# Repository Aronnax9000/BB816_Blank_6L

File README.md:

# BB816_Blank_6L
Blank 6 layer template for BB816 PCB development

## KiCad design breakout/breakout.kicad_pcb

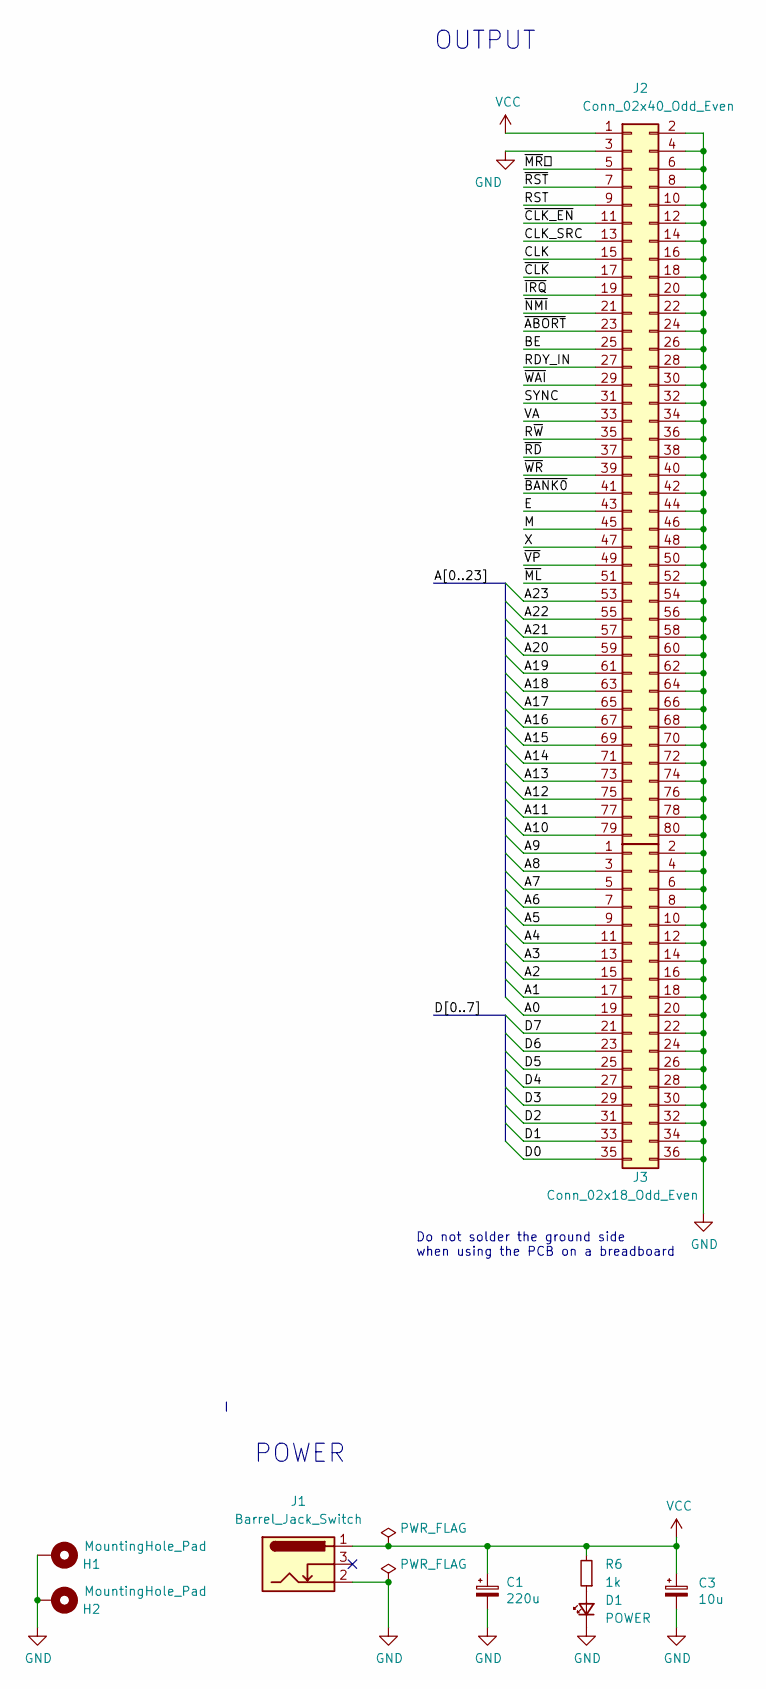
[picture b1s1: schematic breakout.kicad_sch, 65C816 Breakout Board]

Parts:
C1: 220u; CP_Radial_D6.3mm_P2.50mm
C3: 10u; CP_Radial_D4.0mm_P1.50mm
D1: POWER; LED_D3.0mm
H1, H2: MountingHole_Pad; MountingHole_3.2mm_M3_Pad
J1: Barrel_Jack_Switch; BarrelJack_Horizontal
J2: Conn_02x40_Odd_Even; PinHeader_2x40_P2.54mm_Vertical
J3: Conn_02x18_Odd_Even; PinHeader_2x18_P2.54mm_Vertical
R6: 1k; R_Axial_DIN0207_L6.3mm_D2.5mm_P7.62mm_Horizontal

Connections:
/A0: J3.19
/A1: J3.17
/A2: J3.15
/A3: J3.13
/A4: J3.11
/A5: J3.9
/A6: J3.7
/A7: J3.5
/A8: J3.3
/A9: J3.1
/A10: J2.79
/A11: J2.77
/A12: J2.75
/A13: J2.73
/A14: J2.71
/A15: J2.69
/A16: J2.67
/A17: J2.65
/A18: J2.63
/A19: J2.61
/A20: J2.59
/A21: J2.57
/A22: J2.55
/A23: J2.53
/BE: J2.25
/CLK: J2.15
/CLK_SRC: J2.13
/D0: J3.35
/D1: J3.33
/D2: J3.31
/D3: J3.29
/D4: J3.27
/D5: J3.25
/D6: J3.23
/D7: J3.21
/E: J2.43
/M: J2.45
/RDY_IN: J2.27
/RST: J2.9
/R~W: J2.35
/SYNC: J2.31
/VA: J2.33
/X: J2.47
/~ABORT: J2.23
/~BANK0: J2.41
/~CLK_EN: J2.11
/~CLK: J2.17
/~IRQ: J2.19
/~ML: J2.51
/~MR⎒: J2.5
/~NMI: J2.21
/~RD: J2.37
/~RST: J2.7
/~VP: J2.49
/~WAI: J2.29
/~WR: J2.39
GND: C1.2, C3.2, D1.1 (K), H1.1, H2.1, J1.2, J2.2, J2.3, J2.4, J2.6, J2.8, J2.10, J2.12, J2.14, J2.16, J2.18, J2.20, J2.22, J2.24, J2.26, J2.28, J2.30, J2.32, J2.34, J2.36, J2.38, J2.40, J2.42, J2.44, J2.46, J2.48, J2.50, J2.52, J2.54, J2.56, J2.58, J2.60, J2.62, J2.64, J2.66, J2.68, J2.70, J2.72, J2.74, J2.76, J2.78, J2.80, J3.2, J3.4, J3.6, J3.8, J3.10, J3.12, J3.14, J3.16, J3.18, J3.20, J3.22, J3.24, J3.26, J3.28, J3.30, J3.32, J3.34, J3.36
unnamed: D1.2 (A), R6.1
VCC: C1.1, C3.1, J1.1, J2.1, R6.2

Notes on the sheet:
Do not solder the ground side when using the PCB on a breadboard
POWER
OUTPUT

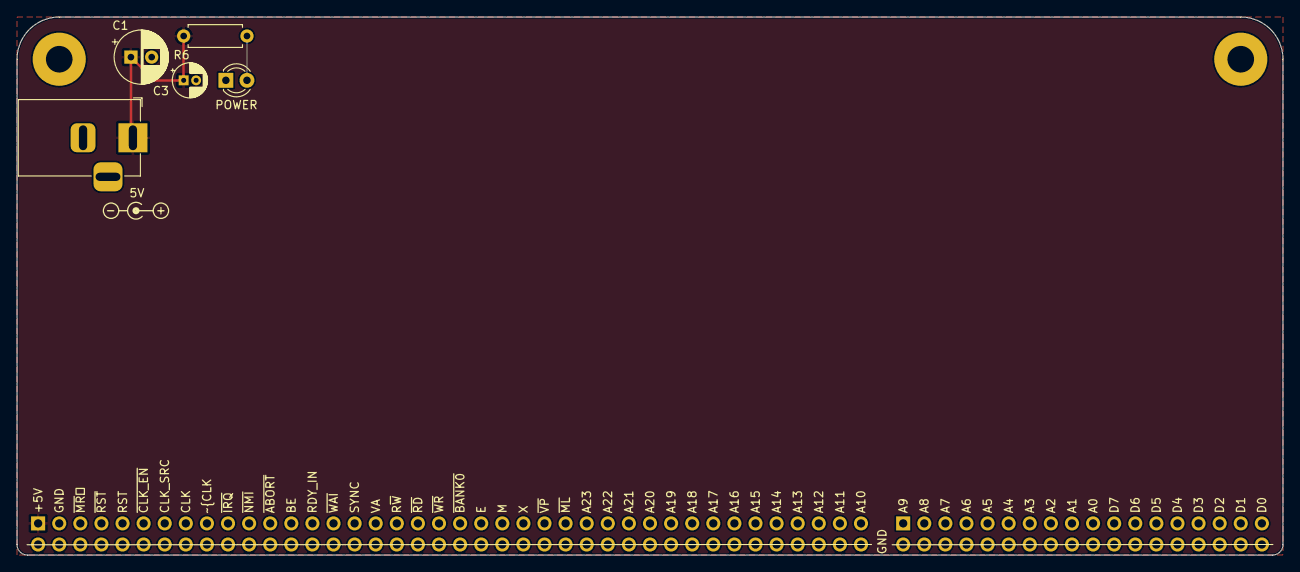
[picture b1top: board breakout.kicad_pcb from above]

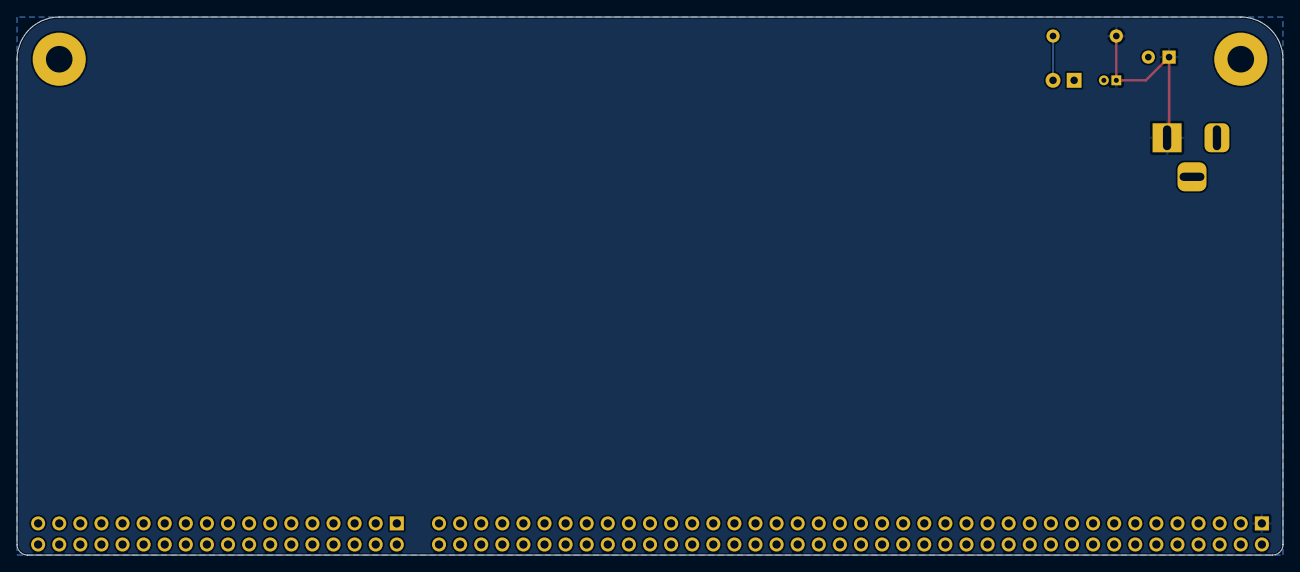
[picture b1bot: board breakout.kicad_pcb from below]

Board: 6 copper layers, 152.4 x 64.8 mm, 9 parts (2 on the bottom side), 3 nets.

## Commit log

2025-03-20 Iniitial upload
2025-03-20 gerbers
2025-03-20 rm lock file

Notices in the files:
breakout/breakout.kicad_pcb:
Licensed under CERN-OHL-W v2
Copyright © 2022 Adrien Kohlbecker
